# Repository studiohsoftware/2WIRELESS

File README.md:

# 2WIRELESS
# Wireless Preset Manager

Connect to your Buchla 200e wirelessly and control it using a web page on your phone or computer. 
Change and save presets, upload and download preset data, and even update module firmware.
</br>
</br>
Call URLs to execute MIDI commands. 
</br>
</br>
Run as USB host, and connect a MIDI USB controller directly to your 200e.
Run as USB device, and connect your DAW directly to your 200e. 

## Preset Manager Commands
- ### http://192.168.0.1/remoteenable
Global remote enable.
- ### http://192.168.0.1/remotedisable
Global remote disable.
- ### http://192.168.0.1/savepreset?preset=(1-30)
Save current settings to specified preset.<br/>
Example: http://192.168.0.1/savepreset?preset=1
- ### http://192.168.0.1/recallpreset?preset=(1-30)
Recall specified preset.<br/>
Example: http://192.168.0.1/recallpreset?preset=29
- ### http://192.168.0.1/getpresets?addr=(module addr in hex)
Retrieve all 30 presets from the specified module.<br/>
Example (259A): http://192.168.0.1/getpresets?addr=0x28
- ### http://192.168.0.1/setpresets?addr=(module addr in hex)
Command specified module to read all 30 presets from on-board non-volatile memory.<br/>
Example (259A): http://192.168.0.1/setpresets?addr=(0x28) <br/> </br>
Use writememory to send presets to on-board non-volatile memory first.
Example HTML here https://github.com/studiohsoftware/2WIRELESS/blob/master/Firmware/SetPresets.html <br/>
Example JSON (for 292e) here https://github.com/studiohsoftware/2WIRELESS/blob/master/Firmware/presetData.json <br/>
## MIDI Commands
- ### http://192.168.0.1/midinoteon?chan=(1-16)&note=(0x0-0x7F)&velo=(0x0-0x7F)
Send MIDI note ON message.<br/> 
Example (Channel 9, note G1, half velocity): http://192.168.0.1/midinoteon?chan=9&note=0x1F&velo=0x40
- ### http://192.168.0.1/midinoteoff?chan=(1-16)&note=(0x0-0x7F)&velo=(0x0-0x7F)
Send MIDI note OFF message.<br/>
Example (Channel 16, note F3, max velocity) http://192.168.0.1/midinoteoff?chan=16&note=0x35&velo=0x7F
- ### http://192.168.0.1/midifinetune?chan=(1-16)&tune=(0x00-0x3F)
Send MIDI fine tune message. <br/>
Example (Channel 1, lowest fine tune -49): http://192.168.0.1/midifinetune?chan=1&tune=0x00<br/>
Example (Channel 2, Ft=An): http://192.168.0.1/midifinetune?chan=2&tune=0x32<br/>
Example (Channel 3, highest fine tune +49): http://192.168.0.1/midifinetune?chan=3&tune=0x63<br/>
- ### http://192.168.0.1/midibend?chan=(1-16)&bend_lsb=(0x0-0x7F)&bend_msb=(0x0-0x7F)
Send MIDI bend command.<br/>
Example (Channel 4, lowest bend): http://192.168.0.1/midibend?chan=4&bend_lsb=0x00&bend_msb=0x00<br/>
Example (Channel 5, no bend): http://192.168.0.1/midibend?chan=5&bend_lsb=0x00&bend_msb=0x40<br/>
Example (Channel 6, highest bend): http://192.168.0.1/midibend?chan=6&bend_lsb=0x7F&bend_msb=0x7F
- ### http://192.168.0.1/midiclockstart
Midi clock start.
- ### http://192.168.0.1/midiclockstop
Midi clock stop.
- ### http://192.168.0.1/midiclock
Midi clock. 24 per beat required.
- ### http://192.168.0.1/sendmidibytes?byte1=(0-0xFF)&byte2=(0x0-0x7F)&byte3=(0x0-0x7F)
Send MIDI command as bytes<br/>
Example (Program Change to change preset to 7):</br>
 http://192.168.0.1/sendmidibytes?byte1=C0&byte2=0x07&byte3=0x00<br/>
Example (Control Change to set fine tune to An on channel 5): </br>
http://192.168.0.1/sendmidibytes?byte1=B4&byte2=0x1F&byte3=0x32<br/>
## Configuration Commands
- ### http://192.168.0.1/ssid
Get wireless SSID<br/>
Returns BUCHLA200E by default.
- ### http://192.168.0.1/ssid=(SSID string)
Set wireless SSID<br/>
Example: http://192.168.0.1/ssid=TEST<br/>
Note ssid limited to 32 characters. 
- ### http://192.168.0.1/password
Get wireless WPA password<br/>
Returns BUCHLA200E by default.
- ### http://192.168.0.1/password=(password string)
Set wireless WPA password<br/>
Example: http://192.168.0.1/password=TEST<br/>
Note password must be at least 8 characters and no more than 63 characters.
- ### http://192.168.0.1/usbMode
Get USB Mode. 1=DEVICE, 0=HOST<br/>
- ### http://192.168.0.1/usbMode=(0-1)
Set USB Mode 1=DEVICE, 0=HOST<br/>
Example: Set USB mode to HOST http://192.168.0.1/usbMode=0<br/>
Note restart required for change to take effect.
- ### http://192.168.0.1/presetname?preset=(1-30)
Get preset name<br/>
Example: get name for preset 12 http://192.168.0.1/presetname?preset=12<br/>
- ### http://192.168.0.1/presetname=(preset name string)&preset=(1-30)
Set preset name<br/>
Example: Set name for preset 5 to "Test" http://192.168.0.1/presetname=Test&preset=5<br/>
- ### http://192.168.0.1/velo?chan=(1-16)
Get velocity enable/disable for MIDI channel.<br/>
Example: Get velocity enable value for channel 2 http://192.168.0.1/velo?chan=2<br/>
- ### http://192.168.0.1/velo=(0-1)&chan=(1-16)
Set velocity enable/disable value for MIDI channel.<br/>
Example: Enable velocity on channel 1 http://192.168.0.1/velo=1&chan=1<br/>
- ### http://192.168.0.1/poly?chan=(1-16)
Get poly enable/disable for MIDI channel.<br/>
Example: Get poly enable value for channel 2 http://192.168.0.1/poly?chan=2<br/>
- ### http://192.168.0.1/poly=(0-1)&chan=(1-16)
Set poly enable/disable value for MIDI channel.<br/>
Example: Enable poly on channel 1 http://192.168.0.1/poly=1&chan=1<br/>
- ### http://192.168.0.1/tran?chan=(1-16)
Get transpose value for MIDI channel.<br/>
Example: Get transpose value for channel 3 http://192.168.0.1/tran?chan=3<br/>
- ### http://192.168.0.1/tran=(-49 to 49)&chan=(1-16)
Set transpose value for MIDI channel.<br/>
Example: Set transpose to -30 on channel 1 http://192.168.0.1/tran=-30&chan=1<br/>
- ### http://192.168.0.1/fine?chan=(1-16)
Get fine tune value for MIDI channel.<br/>
Example: Get fine tune value for channel 3 http://192.168.0.1/fine?chan=3<br/>
- ### http://192.168.0.1/fine=(-49 to 49)&chan=(1-16)
Set fine tune value for MIDI channel.<br/>
Example: Set fine tune to An on channel 1 http://192.168.0.1/fine=0&chan=1<br/>
Example: Set fine tune to 30 on channel 5 http://192.168.0.1/fine=30&chan=5<br/>
- ### http://192.168.0.1/mask?chan=(1-16)
Get bus mask for MIDI channel.<br/>
Example: Get mask value for channel 3 http://192.168.0.1/mask?chan=3<br/>
- ### http://192.168.0.1/mask=(0x0-0xF)&chan=(1-16)
Set mask value for MIDI channel.<br/>
Example: Route channel 1 to all four 200e buses http://192.168.0.1/mask=0xF&chan=1<br/>
Example: Route channel 1 to bus A http://192.168.0.1/mask=0x8&chan=1<br/>
Example: Route channel 1 to bus B http://192.168.0.1/mask=0x4&chan=1<br/>
Example: Route channel 1 to bus C http://192.168.0.1/mask=0x2&chan=1<br/>
Example: Route channel 6 to bus D http://192.168.0.1/mask=0x1&chan=6<br/>
## Utility Commands
- ### http://192.168.0.1/readmemory?addr=(0x0-0x03FFFF)&length=0-262143
Read bulk data from on-board non-volatile memory.<br/>
Example (Address 0x1C, return 32 bytes. Note 0x001C, or 0x00001C also acceptable): http://192.168.0.1/readmemory?addr=0x1C&length=32
- ### http://192.168.0.1/writememory?addr=(0x0-0x03FFFF)&data=(hex string)
Write data to on-board non-volatile memory at the specified address.<br/>
Example: (Address 0x1ABCD, five data bytes 0AFF1B0432) http://192.168.0.1/writememory?addr=0x1ABCD&data=0AFF1B0432<br/>
Note all addresses below 0x02C000 are used as scratch space by preset and firmware transfers. 
- ### http://192.168.0.1/writememory
Write bulk data to on-board non-volatile memory.<br/>
Note this is an HTTP POST with a JSON formatted body.<br/> 
Example JSON here https://github.com/studiohsoftware/2WIRELESS/blob/master/Firmware/writeMemoryExample.json<br/>
Notes:
- #### 20k byte JSON file limit.
- #### Addresses are arbitrary locations within 0x0-0x03FFFF.
- #### Data elements can be up to 256 bytes long each (512 characters).
- #### All addresses below 0x02C100 are used as scratch space by preset and firmware transfers. 
## V2 Firmware Support
Old firmware (pre Primo version) also supported. Simply add a "v2" to the URL path. <br/>
Example: http://192.168.0.1/v2/remotedisable<br/>

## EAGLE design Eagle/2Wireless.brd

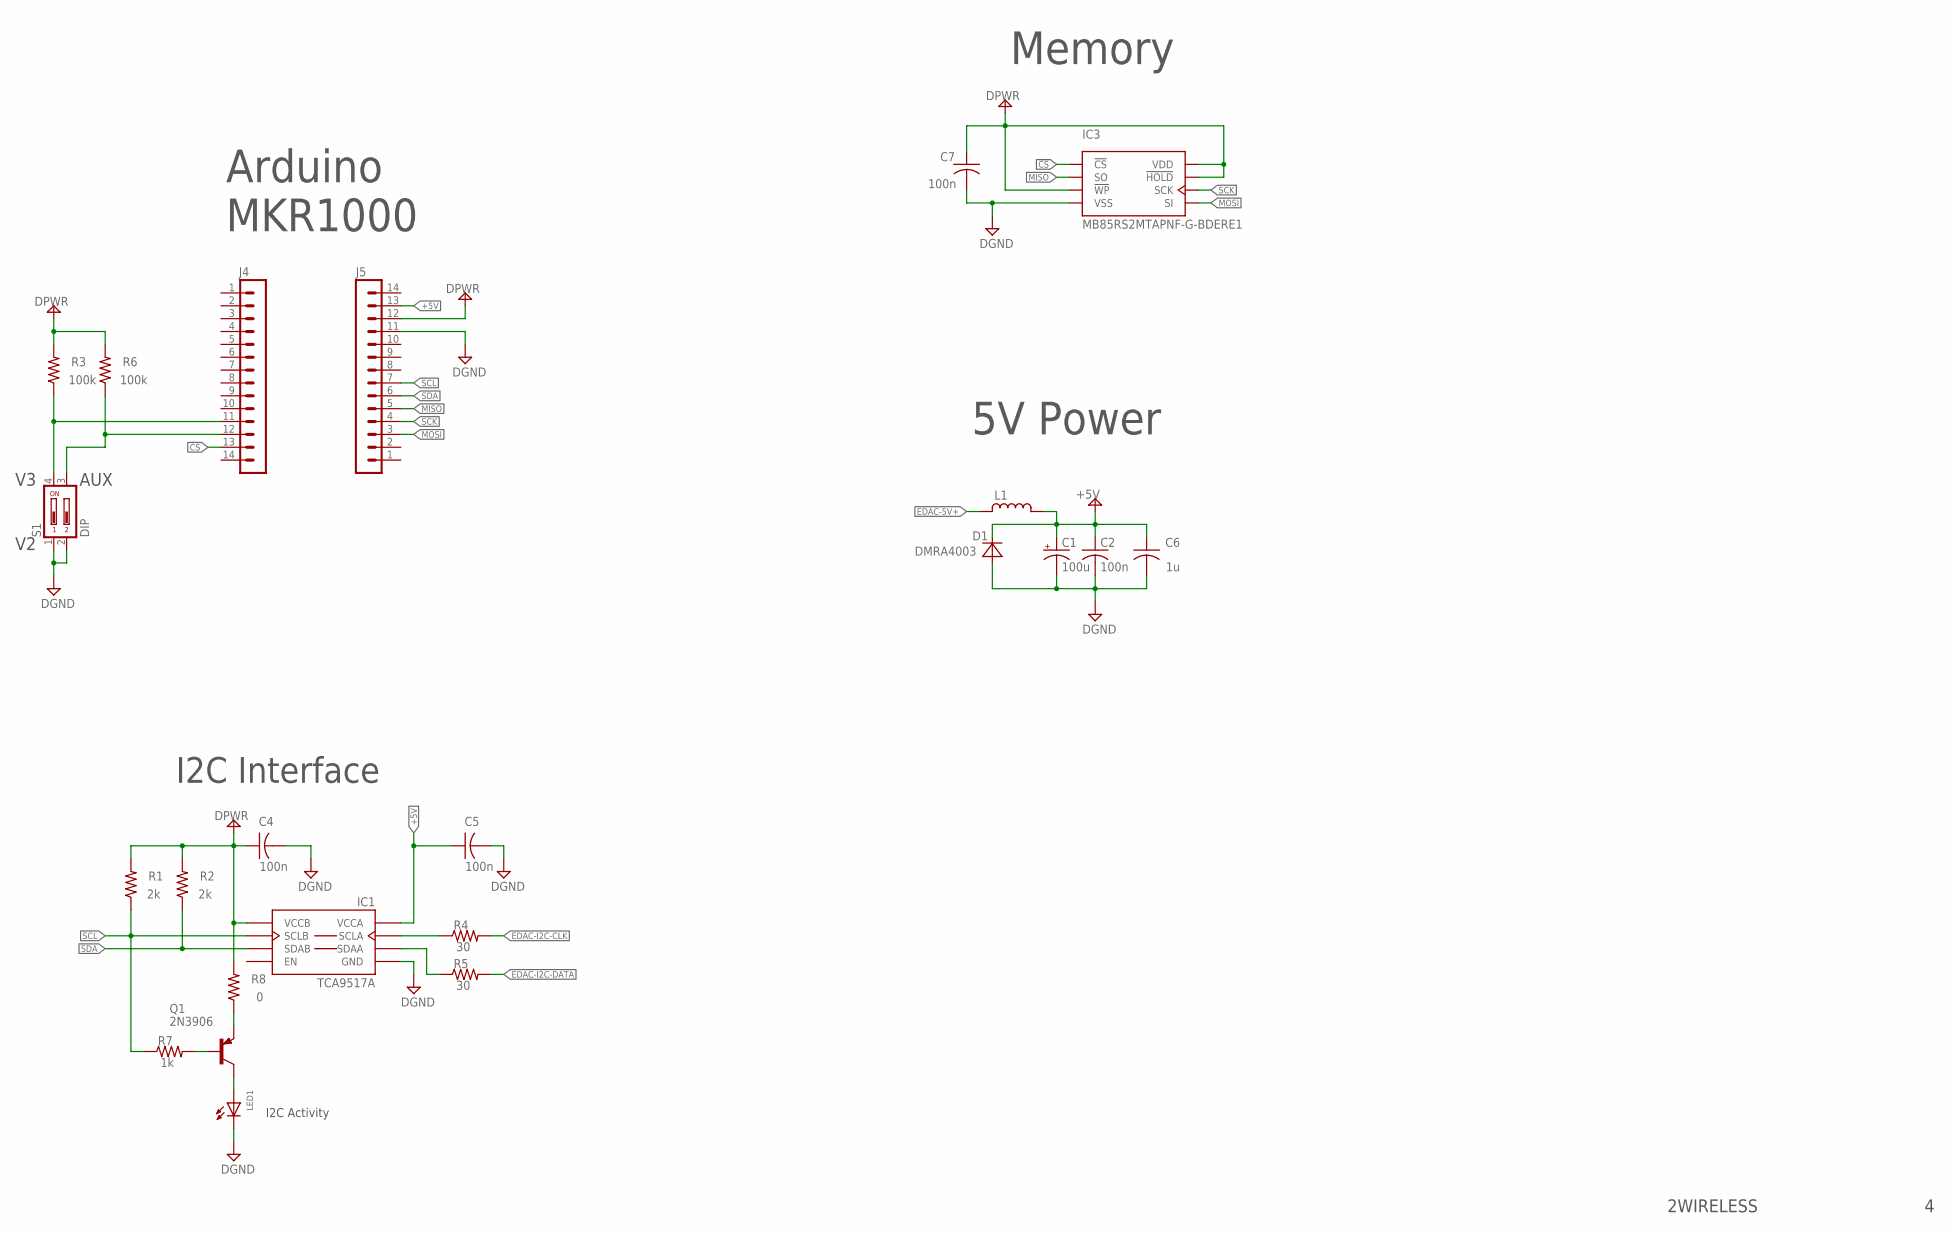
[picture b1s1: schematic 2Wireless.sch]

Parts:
C1: 100u; PAN-D
C2, C4, C5, C7: 100n; C0603
C6: 1u; C0603
D1: DMRA4003; SMA
IC1: TCA9517A; MSOP8
IC3: MB85RS2MTAPNF-G-BDERE1; SO08
J4, J5: MA14-1
L1: LB; 0603
LED1: LED0805BLUE; CHIPLED_0805
Q1: 2N3906; SOT23
R1, R2: 2k; R0603
R3, R6: 100k; R0603
R4, R5: 30; R0603
R7: 1k; R0603
R8: 0; R0603
S1: DIP; CTS-219-02

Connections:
!CS: IC3.1 (!CS), J4.13
+5V: C1.+, C2.1, C5.1, C6.1, D1.K (C), IC1.1 (VCCA), J5.13, L1.2 (4)
DGND: C1.-, C2.2, C4.2, C5.2, C6.2, C7.2, D1.A, IC1.4 (GND), IC3.4 (VSS), J5.11, LED1.C, S1.1, S1.2
DI-AUX: J4.12, R6.1, S1.3
DI-VERSION: J4.11, R3.1, S1.4
DPWR: C4.1, C7.1, IC1.8 (VCCB), IC3.3 (!WP), IC3.7 (!HOLD), IC3.8 (VDD), J5.12, R1.2, R2.2, R3.2, R6.2, R8.2
EDAC-5V+: L1.1
EDAC-I2C-CLK: R4.2
EDAC-I2C-DATA: R5.2
MISO: IC3.2 (SO), J5.5
MOSI: IC3.5 (SI), J5.3
unnamed: Q1.1 (B), R7.2
unnamed: LED1.A, Q1.2 (C)
unnamed: Q1.3 (E), R8.1
unnamed: IC1.2 (SCLA), R4.1
unnamed: IC1.3 (SDAA), R5.1
SCK: IC3.6 (SCK), J5.4
SCL: IC1.7 (SCLB), J5.7, R1.1, R7.1
SDA: IC1.6 (SDAB), J5.6, R2.1

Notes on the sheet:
2WIRELESS
5V Power
Memory
Arduino MKR1000
I2C Interface
AUX
I2C Activity

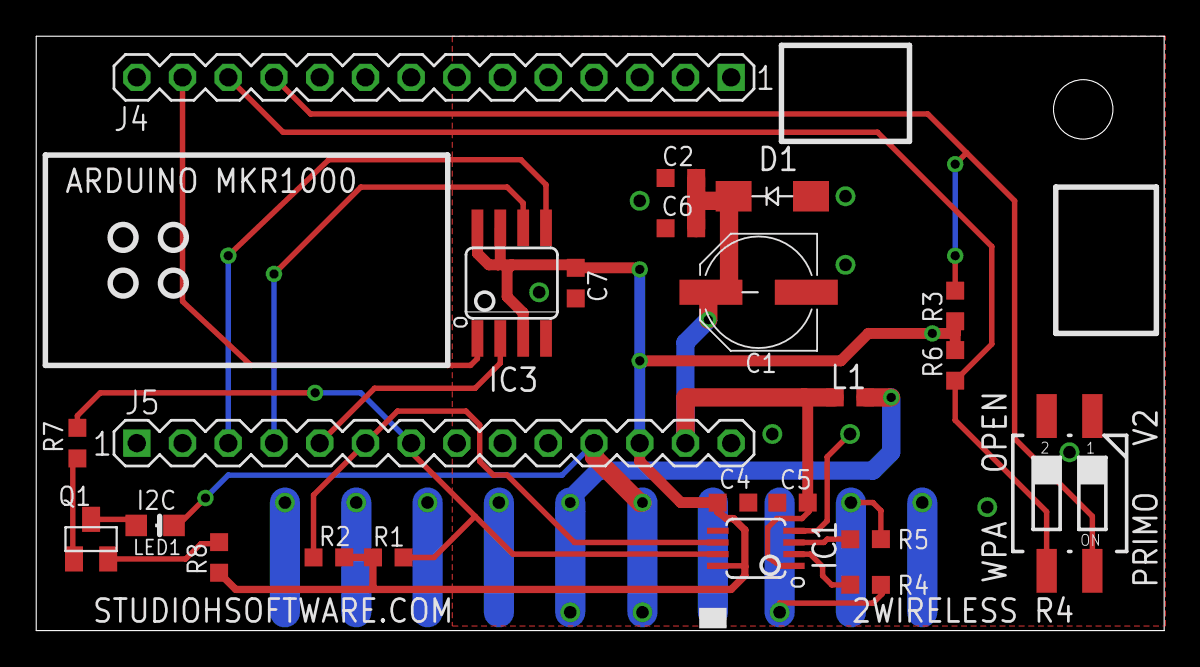
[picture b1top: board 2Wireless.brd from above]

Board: 2 copper layers, 62.7 x 33.0 mm, 23 parts (0 on the bottom side), 16 nets.

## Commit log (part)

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2019-08-12 Create Test
2019-08-12 Original version.
    Device will appear as a wireless access point. Connect and navigate to http://192.168.0.1.
    Note calls to System.set SYSTEM_CONFIG_SOFTAP_DISABLE_BROADCAST enable and disable the SSID broadcast for security. These options must be commented out unless Particle Workbench is used to local comp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
2019-08-16 Remove cpp file and unused README.md
2019-08-16 Initial preset bus test remote enable/disable working. Choose red to enable, any other color to disable.
    Note order of include files at the top is important.
2019-08-18 Add remote enable/disable URLs.
    Investigate fetching preset data from 291e, but I don't think I can do mulitple master without modifying the core. Hoping to avoid that. Note also that Photon has only one I2C device.
2019-08-18 Preset data received from 291e using getpresetdata.
    However, I chop it off after 10 bytes so it freezes the bus when switching back to master because the 291e is still talking. Need to actually read bytes in and look for terminating byte sequence from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
2019-08-19 REST call /getpresets?addr=<hex addr> seems to be working.
    Note that timer was used (unfortunately) to determine when the received byte stream is done. Modules send end backup message, but it is general call, which appears to be yet unsupported for Wire libr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
2019-08-22 Added ring buffer and new commands recallpreset and savepreset.
    Note that guarding the ring buffer access in receiveEvent() did not work. Any blocking there interfered with I2C processing and hung the Photon. I tried WITH_LOCK, TRY_LOCK, and various mutex strateg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
2019-08-23 Add midi note on command. Other midi commands staged for URL handlers.
2019-08-25 Complete URL implementation for remaining midi calls.
2019-08-26 Remove check for unused bytes before writing to ring buffer in receiveEvent. Hopefully this eliminates occasional I2C hang during getpresets.
2019-09-09 Added writememory and readmemory functions.
2019-09-19 Added URL writefirmware, added draft html POST example WriteFirmware.html, and test data test.hex.
    Currently just echoes the data opened in test.hex back to the browser.
2020-04-21 Get presets now working.
    Cleaned up getpresets, and added optional length parameter to place carriage returns in result for teasing out patterns in the preset data.
    Added bin files so that everything can be flashed via command line in DFU mode.
    Modified readmemory and writememory for new 2M FRAM chip. 256K bytes now available. Note this breaks three prototype units already in the field which are running on 32K byte version.
2020-04-21 Problem with last commit. Trying again.
2020-04-21 Fix readme for new 256k byte FRAM.
2020-04-21 Add binaries for command line DFU flash.
2020-04-25 Check in to save work on writing presets.
    JSON parser working on example 292e preset file.
    Discovered maximum POST side of 20400 to the Photon.
    Also some work on I2C reads from master. Untested.
2020-04-28 Setpresets working for 292e.
2020-04-28 Update README.md.
2020-04-28 Fix JSON formatting errors. Add GetPresets.html.
2020-04-29 Finish post processing of 292e preset data.
2020-04-29 Add 251e to GetPresets.html.
    Minor cleanup on 2Wireless.ino.
2020-05-01 Checking in to save html files.
    SetPresets not working due to hardware limitations.
2020-05-02 Added two 24FC512. Photon unreliable as I2C slave.
2020-05-02 Add two more 24FC512.
2020-05-04 Added fix to rxBuffer within i2c_hal.c.
    Removed bool parameter from OnRequest.onRequest
    Tested framRead within OnRequest.
2020-05-04 291e Get/SetPresets now working.
2020-05-04 SetPresets cleanup.
2020-05-05 Fixed 251e in GetPresets.html.
2020-05-06 Modules added to GetPresets.html
2020-05-07 Added DPO and 255e to GetPresets.html
2020-05-10 Firmware V1 JSON done. Draft of V2.
2020-05-11 Fixed up WriteFirmware.html based on 251e.
    Modified OnRequest to handle 1-3 address bytes.
2020-05-11 Change readmemory/writememory.
    Now use readbyte/writebyte.
2020-05-11 Split JSON into small chunks in WriteFirmware.html.
2020-05-12 Change preset range to from 0/29 to 1/30
    Cleanup getFirmwareVersion in WriteFirmware.html
2020-05-12 WriteFirmware.html now sends multiple parts.
2020-05-12 WriteFirmware.html now writes to FRAM.
2020-05-13 Decouple memorywrite from setpresets.
2020-05-13 Clean up WriteFirmware.html.
2020-05-13 Better JSON splitting in WriteFirmware.html.
2020-05-13 Remove 24FC512 chips. Not needed.
2020-05-13 Fix comments and typos.
2020-05-15 Rewrite SetPresets.html to display status.
2020-05-15 Clean up display on GetPresets.html.
2020-05-15 Attempt to adjust for mobile display.
2020-05-15 Attempt to adjust for mobile.
2020-05-15 Adjust GetPresets.html for mobile.
2020-05-16 Add Save link to GetPresets.html
2020-05-16 Add status text display to WriteFirmware.html.
2020-05-16 Fix font on WriteFirmware.html.
2020-05-17 Update save/recall on PresetManager.html.
2020-05-17 Improve buttons on PresetManager.html
2020-05-17 Adjustments to PresetManager.html
2020-05-18 Set PresetManager.html to index page.
2020-05-19 Add readmemory for bulk read.
2020-05-19 Add writememory GET version.
    Remove readbyte and write byte.
2020-05-19 Change PresetManager.html baseAddr.
2020-05-19 Add screenshot of homepage.
2020-05-20 Add warning message to GetPresets.html
2020-05-22 Increase ring buffer from 2400 to 4800.
    Larger preset volumes were getting corrupted.
    New max post size is 19k (was over 20k).
    Also added 206e and 261e to GetPresets.html.
2020-05-23 Send remote disable on startup to unlock 206e
    Also set on board D7 LED to light up during I2C
    READ operations so that you can tell a firmware
    load is in progress.
2020-05-23 Added 250e.
2020-05-26 Add 210e, 227e, 256e, 296e to GetPresets.html.
2020-06-05 Add v2 firmware support.
2020-06-17 Add Primo/V2 version switch.
2020-07-01 Add primo/v2 hardware switch.
    Hide version radio buttons.
2020-07-18 Add RS232 Connector for future use.
2020-07-22 Switch layout from Photon to Arduino MKR1000.
2020-08-09 Add I2C pullups to MKR1000 layout.
2020-08-29 move examples to docs folder
2020-08-29 indentation
2020-08-29 use a json hash
2020-09-02 cleanup some text interpolation
2020-09-03 use html lint, clean styles, tidy html
2020-09-03 use update button names
2020-09-07 Add VS Code project config files.
2020-09-07 Create separate photon and arduino areas.
2020-09-08 Added stubs for remoteenable and remotedisable.
2020-09-08 Changes to url processing.
2020-09-08 Added stubs for all urls.
2020-09-08 Fixed bug in generate_204 case.
2020-09-13 add gitignore some tidying
2020-09-13 add macos setup scripts configs move dirs
2020-09-13 index.js
2020-09-14 Change power source on TCA9517A.
2020-09-16 Add labels to aux switch for open/wpa.
2020-09-26 Remove triggerRemoteEnable approach. I2C broken.
2020-09-29 Add 10 uS delay before switching I2C modes.
2020-09-30 HTTP response chunking now working.
2020-09-30 PresetManager homepage working on MKR1000.
2020-10-01 Add MIDI commands for MKR1000.
2020-10-01 POST version of writememory on MKR1000.
2020-10-01 WIFI and VERSION switches MKR1000.
    Also have GetPresets.html working, but buffer overrun on 251e.
2020-10-03 GetPresets.html working on MKR1000.
    Ring buffer could not keep up with the preset data coming in from the
    module. Writing to FRAM worked, but reading adds time, and total for
    the 251e is about 20 seconds. Timeout on GetPresets.html increased to
    30 seconds. Could be improved using the FSTRD mode of the FRAM chip.
    Checking in to save since it all seems to be working.
2020-10-04 SetPresets.html working MKR1000.
2020-10-15 Add stub for setup page.
2020-10-21 Lower max transfer size in WriteFirmware.html.
    Photon running out of memory.
    Also, MKR1000 firmware update not working.
2020-10-21 MKR1000 now supports firmware updates too.
2020-10-21 Removed unused RingBuffer class.
2020-10-22 FRAM doc reserves opt homepage start addr and len.
2020-10-26 SSID now configurable.
2020-10-26 Fix README.md formatting.
2020-10-27 Add password configuration.
2020-10-30 Added setup page to 192.168.0.1/setup
2020-11-04 WriteHomepage.html in progress.
2020-11-05 Change WriteHomepage.html to WriteUserPage.html
2020-11-05 WriteCustomPage.html working, but no space to use.
2020-11-07 More robust password/ssid initialization.
2020-12-13 Add MIDIUSB device handler for testing.
2020-12-16 Add USB Host and Device for testing.
2020-12-16 Add RingBuffer for USB Host data.
2020-12-17 USB now putting messages on 200e bus.
2020-12-17 Add URL for generic midibytes command.
    Also, change MIDI urls to use chan instead of mask.
2020-12-17 Current preset now tracked in firmware.
    Changing presets by program change,
    or by recallpreset URL both track current
    preset now.
2020-12-18 Working on MIDI config and fram cleanup.
2020-12-19 Store MIDI config in FRAM.
    Poly mode for MIDI ON/OFF done
    but untested.
2020-12-19 Add presetname URL getter/setter
2020-12-19 Add currentpreset URL.
2020-12-20 Added getter/setter URLs for MIDI params.
2020-12-20 Rename midibytes to sendmidibytes.
2020-12-20 Fix typos.
2020-12-20 Add headings
2020-12-20 Add device description.
2020-12-20 Formatting changes.
2020-12-21 Add URL to get/set usbMode (HOST/DEVICE).
2020-12-21 Remove read/write memory from PresetManager.html
2020-12-22 Added MIDI table to setup page.
2020-12-22 Send fine tune when setFine called.
2020-12-23 Add Bus table to setup page.
2020-12-24 Put fine tune back into setup data.
    New buses array fully supports r/w.
2020-12-29 Add more timeout to switch to slave.
    Also bug on poly bus D fixed.
2020-12-30 Polyphonic now working.
2020-12-31 Add MIDI CC messages for preset manager functions.
    Also handle undefined case in preset names.
2021-01-12 Add hole for standoff.
2021-01-23 Increase hole size for standoff.
2021-02-02 Add VID/PID and display version on setup page.
2021-03-15 Add Poll On Startup option for PRIMO.
2021-04-14 Add corrected adapter image to installation.png
2021-04-18 Fix USB device enum problem on cable reconnect.
2021-04-26 Check in for send Midi and prg change enable.
    Still need to add options to Setup.html
2021-04-26 Add option to disable MIDI Program Change
    Attempt to send 252e MIDI clock locks up everything.
    Feature removed from Setup.html for now.
2021-05-10 Neuter 252e clock publishing.
    Test caused lockup. 2nd USB pipe probably reqd.
    Note WPM hanging after WriteFirmware, and LED not flashing.
    Also WriteFirmware often fails, requiring many attempts.
2021-09-18 Clear mem locs 0x20-0x4F for v1 firmware flash.
2021-10-27 Add option to publish 252e MIDI clock over USB.
    Supported in USB Device mode only.
2021-12-22 Improved installation instructions.
2021-12-22 Added image with white background.
2022-01-25 Change from readName to readNames in PresetManager
    Fixes hang at PresetManager page refresh.
2022-01-25 Fix %20 problem in preset names.
2022-07-28 Remove condition on preset recall in PresetManager.
2023-08-03 Add 207e
2023-08-06 Add 206e
2023-08-06 Add comment regarding AP disconnect. Test commit.
2024-04-21 Add WPMCore files
2024-06-02 Update 2Wireless.ino
    Added null pointer fix
2024-06-07 Moved empty reference to better location
2024-06-07 Update 2Wireless.ino to v1.9
    Wifi reconnect fixed
2024-06-12 Fix Wifi Reconnect
2024-12-31 Wrong bin file uploaded. Now v1.9
2025-06-30 Add firmware display, favicon, improved bus stability.
2025-07-01 Restore check for sendMidiToUsb in I2C listener.
2025-07-01 Restore maxdelays in masterEndTransmission
2025-07-03 Stabilization for heavy bus activity
2025-07-04 Improved debugging
2025-07-19 Fetch setup data in two chunks instead of one.
2026-03-02 Fix message corruption.
2026-03-02 Add offline favicon.ico for fun.
    Offer favicon.ico for offline web pages. Just make sure the ico file is in the same directory as the html files on your computer/phone.
    Also adjusted a couple of module formats in GetPresets,html because they seemed to be out of sync.
2026-03-03 Add bus checks to all messages.
